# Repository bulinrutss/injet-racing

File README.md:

# INJET RACING

ECU de injeção para TBI (corpo de borboleta), Fase 1. Mede ar por velocidade e pressão (speed-density), calcula o tempo de injeção e aciona até quatro bicos em batch-fire. O cérebro é uma **Black Board STM32F407VET6** encaixada na placa; a fonte de 5 V fica na própria ECU.

A placa em curso é a **prodv6** (240 × 160 mm, duas camadas). O firmware em `firmware/` lê sensores, calcula o pulso e registra na serial. Ainda não dispara os bicos.

## Como funciona

A bateria entra por proteção (fusível, MOSFET contra inversão e TVS) e vira **+12V_PROT**. Esse 12 V alimenta bicos, bobinas de relé e o aquecedor da sonda pelo chicote. Um módulo **MP1584** gera **+5 V** para a Black Board, o MAP e os amplificadores da lambda. O 3,3 V sai do regulador interno da Black Board e é só distribuído na placa (sensores, pull-ups, opto de RPM). Não há um segundo LDO na ECU.

```
+12 V bateria
    │
    ├─ proteção ── +12V_PROT ── bicos (lado +), relés, aquecedor λ
    │
    └─ MP1584 ── +5 V ── Black Board ── +3V3 ── sensores e lógica
```

Cada volta do motor chega pelo **negativo da bobina**, isolado por um opto **PC817**. Com RPM, MAP, temperatura do ar e tensão da bateria, o firmware estima a massa de ar, aplica uma eficiência volumétrica (VE) e soma o tempo morto do bico. A sonda **LSU 4.2** (wideband, frente analógica com MCP6002 e OPA388IDR) devolve lambda; um PI corrige o pulso em até ±15 % com o motor quente e fora de plena carga. Os bicos são low-side: o chicote leva +12 V e a placa fecha o negativo com **IRLZ44N**. Três **2N7000** comandam relés externos (principal, bomba e IAC) pelo conector CN3. O relé em si não é soldado na placa.

Gravação e debug são pela USB da Black Board. Não há conector SWD na ECU.

| Ação | 12 V na ECU | Cabo USB |
|------|-------------|----------|
| Gravar firmware | desligado | normal |
| Monitor serial / tune | ligado | power blocker (só D+, D− e GND) |
| No carro | ligado | desconectado |

Serial de bancada: **115200 baud**.

## Estado agora

| Bloco | Situação |
|-------|----------|
| Proteção de 12 V e buck +5 V (MOD3–4) | roteado na prodv6 |
| Black Board, +3V3 e referência (MOD5) | roteado |
| Sensores IAT, CLT, MAP, TPS, tensão de bateria (MOD6) | roteado até os headers da Black Board |
| RPM pelo negativo da bobina (MOD7) | roteado, CN1-22 → PC817 → PE8 |
| Quatro injetores IRLZ44N (MOD8) | roteado, CN1-13…16 |
| Três drivers de relé + CN3 (MOD9) | roteado; SRD fica no chicote |
| Lambda e aquecedor (MOD11–12) | roteado |
| CAN (MOD10) | desativado nesta revisão |
| DRC, silk e Gerber | em aberto (clearance do OPA388, contorno da placa, unconnected cosmético) |
| Bancada sem motor | roteiro em `kicad/prodv6/BENCH-CHECKLIST.md`, ainda não é validação de rua |
| Firmware | referência de bancada: lê, calcula e loga; o pulso não sai nos MOSFETs |
| prodv7 | cópia da prodv6 com o OPA388 em DIP-8 no lado dos componentes |

O DRC da prodv6 ainda não está zerado. O checklist de layout e os scripts `_check_modN_now.py` estão em `kicad/prodv6/`.

## Placa

Abrir no KiCad 8:

`kicad/prodv6/injet-racing-prodv6.kicad_pro`

Salvar o PCB não mexe no esquemático. Atualizar o PCB a partir do esquemático é o F8. Não rodar o gerador Python por cima do `.kicad_pcb`: ele apaga trilhas e zonas já feitas.

A prodv7 (`kicad/prodv7/`) existe para trocar o OPA388 de SOIC na face de baixo por DIP-8 furado. O desenho de trabalho continua sendo a prodv6 até essa troca fechar.

### Conectores da prodv6

Pinagem que os scripts de checagem conferem na placa roteada. O restante do chicote está em `modulo/esquema-eletrico.md` §9.

**CN1** — header ATX 24 pinos (alimentação, sensores, RPM, bicos):

| Pinos | Função |
|-------|--------|
| 1–2 | +12V_BAT |
| 3 | +5 V (MAP) |
| 4 | +3V3 (TPS e pull-ups) |
| 6 | IAT |
| 7 | CLT |
| 8 | MAP |
| 10 | TPS |
| 11 | +12V_PROT (divisor de bateria) |
| 13–16 | INJ1…INJ4 (low-side) |
| 22 | RPM, negativo da bobina |

**CN2** — PCIe 6 pinos, sonda LSU:

| Pino | Função |
|------|--------|
| 1 | +12V_PROT, aquecedor H+ |
| 2 | H− (dreno do MOSFET) |
| 3 | sem ligação |
| 4 | IP |
| 5 | VM |
| 6 | UN |

**CN3** — PCIe 6 pinos, contato NA dos relés externos:

| Pino | Função |
|------|--------|
| 1 | IAC |
| 2 | bomba |
| 3 | relé principal |
| 4 | GND |

### GPIO da Black Board

Definidos em `firmware/include/pins.h` e no esquemático.

| Sinal | Pino |
|-------|------|
| IAT / CLT / MAP / TPS / VBat | PD0 / PA9 / PC9 / PC8 / PA8 |
| Lambda Vm, Ip, Un, Ri | PA4 / PA5 / PA6 / PE2 |
| Aquecedor | PB0 |
| RPM | PE8 |
| INJ1…4 | PE9, PE11, PE13, PE15 |
| Relé principal / bomba / IAC | PD10 / PD8 / PD9 |

## Firmware

Alvo: STM32F407VET6 pela core STM32duino (placa Generic F407VET6 ou equivalente da Black Board). Os fontes estão em `firmware/src/`; não há `platformio.ini` no repositório.

O `loop` faz isto a cada passagem:

1. Atualiza a wideband (aquecedor pela resistência da célula, corrente de bomba, lambda).
2. Lê MAP, TPS, CLT, IAT e bateria.
3. Atualiza o trim de lambda.
4. A cada 10 ms calcula o tempo de injeção em ms.
5. A cada 100 ms imprime `RPM MAP TPS CLT VBat L PW TRIM`.

O que esse código ainda não faz: agendar o pulso nos quatro MOSFETs (há um TODO no `main.cpp`), tabela VE de verdade (`fuelVeLookup` devolve 0,75 fixo) e protocolo de tune. A interrupção de RPM guarda o período; quem publica o valor filtrado é `rpmUpdate()`, e o `loop` ainda não chama essa função — por isso o campo RPM da serial fica em zero. A bomba é ligada no `setup` e permanece ligada.

Cilindrada, vazão dos bicos e número de cilindros em `fuel.cpp` / `pins.h` são constantes de bancada, não o acerto de um motor específico.

## Mapa do repositório

| Pasta | Conteúdo |
|-------|----------|
| `modulo/` | Esquema elétrico, listas de componentes, sensores, bicos, lambda, pinout e flanges |
| `kicad/prodv6/` | PCB atual, checklist, bancada e scripts de checagem |
| `kicad/prodv7/` | Variante com OPA388 em DIP-8 |
| `kicad/` | Esquemático hierárquico e PCBs anteriores (prod … prodv5) |
| `firmware/` | Firmware de referência da Fase 1 |
| `implementacoes-futuras/` | Ideias fora da Fase 1 (3-step, relé pesado, roda fônica, condicionador VR) |
| `projetos piloto/` | Produtos à parte, hoje o limitador 3-step |
| `assets/` | Renders e estudos de placa de uma camada |

Na raiz também estão o manual e a lista de TBI compatíveis (PDFs).

Itens de `implementacoes-futuras/` e de `projetos piloto/` ficam fora da prodv6 até serem puxados para o escopo.

## Licença

MIT. Copyright (c) 2026 Marcos Gasperin. Ver `LICENSE`.

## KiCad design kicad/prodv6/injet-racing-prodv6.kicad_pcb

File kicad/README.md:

# KiCad — INJET RACING ECU (Fase 1)

Projeto esquemático hierárquico gerado a partir de `modulo/esquema-eletrico.md`.

## Abrir

1. Instale [KiCad 8](https://www.kicad.org/download/) (ou 7 — formato compatível)
2. Abra **`injet-racing-ecu.kicad_pro`** no KiCad
3. No **Eeschema**, navegue pelas folhas na barra lateral ou duplo-clique nos blocos

## Folhas

| Página | Arquivo | Conteúdo |
|--------|---------|----------|
| 1 | `injet-racing-ecu.kicad_sch` | Índice hierárquico (blocos) |
| 2 | `sheets/power.kicad_sch` | 12V → fusível → IRF9540 → TVS → **MP1584** → +5V |
| 3 | `sheets/mcu.kicad_sch` | **Black Board** U1 + REF3033 + barra +3V3 |
| 4 | `sheets/sensors.kicad_sch` | IAT/CLT/MAP/TPS/VBat + CN1 ATX-24 |
| 5 | `sheets/rpm.kicad_sch` | PC817 opto (negativo bobina) |
| 6 | `sheets/injectors.kicad_sch` | 4× IRLZ44N low-side |
| 7 | `sheets/relays.kicad_sch` | 3× relé (principal/bomba/IAC) |
| 8 | `sheets/lambda.kicad_sch` | MCP6002 + OPA388IDR + heater + CN2 PCIe-6 |
| 9 | `sheets/can.kicad_sch` | SN65HVD230 transceiver |

## Regenerar

```powershell
cd kicad
pip install sexpdata
python _gen_kicad_ecu.py
```

## Notas

- **Símbolos embutidos** na biblioteca `Injet:*` — não precisa instalar libs externas para abrir
- **PCB vazio** — próximo passo: importar netlist e rotear (fenolite 1-layer ou PCB futuro)
- Após abrir, rode **Ferramentas → Associar footprints** e **Inspectar → Regras elétricas (ERC)**
- Se o KiCad pedir migrar formato, aceite — salve de volta na mesma pasta
- Pinagem GPIO = `firmware/include/pins.h` e `esquema-eletrico.md` §2.0

## Alimentação (resumo)

```
+12V_BAT → proteção → +12V_PROT
                    → MP1584 → +5V → Black Board pin 5V
                                      ↓ LDO interno
                                    +3V3 → barra ECU → sensores/CAN/opto
```

Não há AMS1117 extra na placa ECU — ver `esquema-eletrico.md` §1.4.

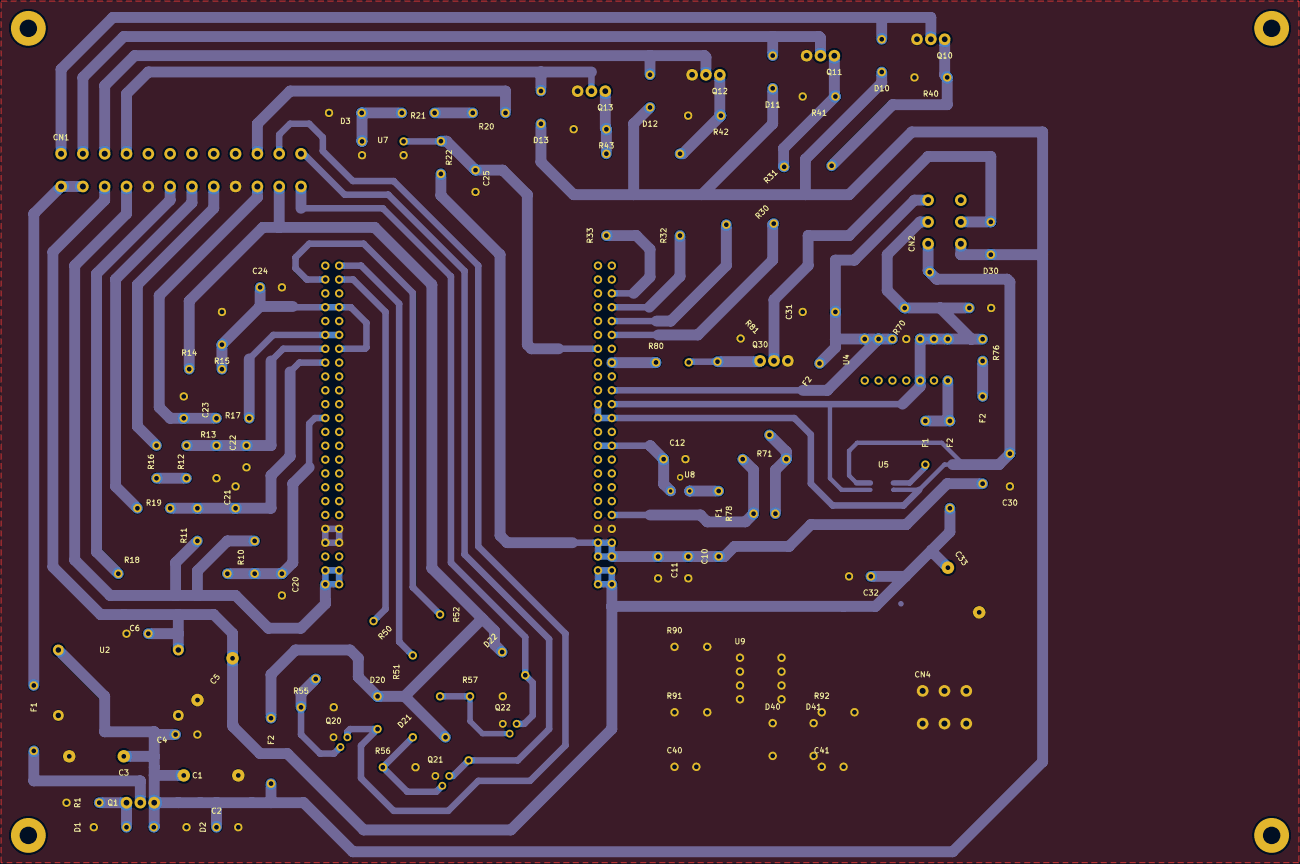
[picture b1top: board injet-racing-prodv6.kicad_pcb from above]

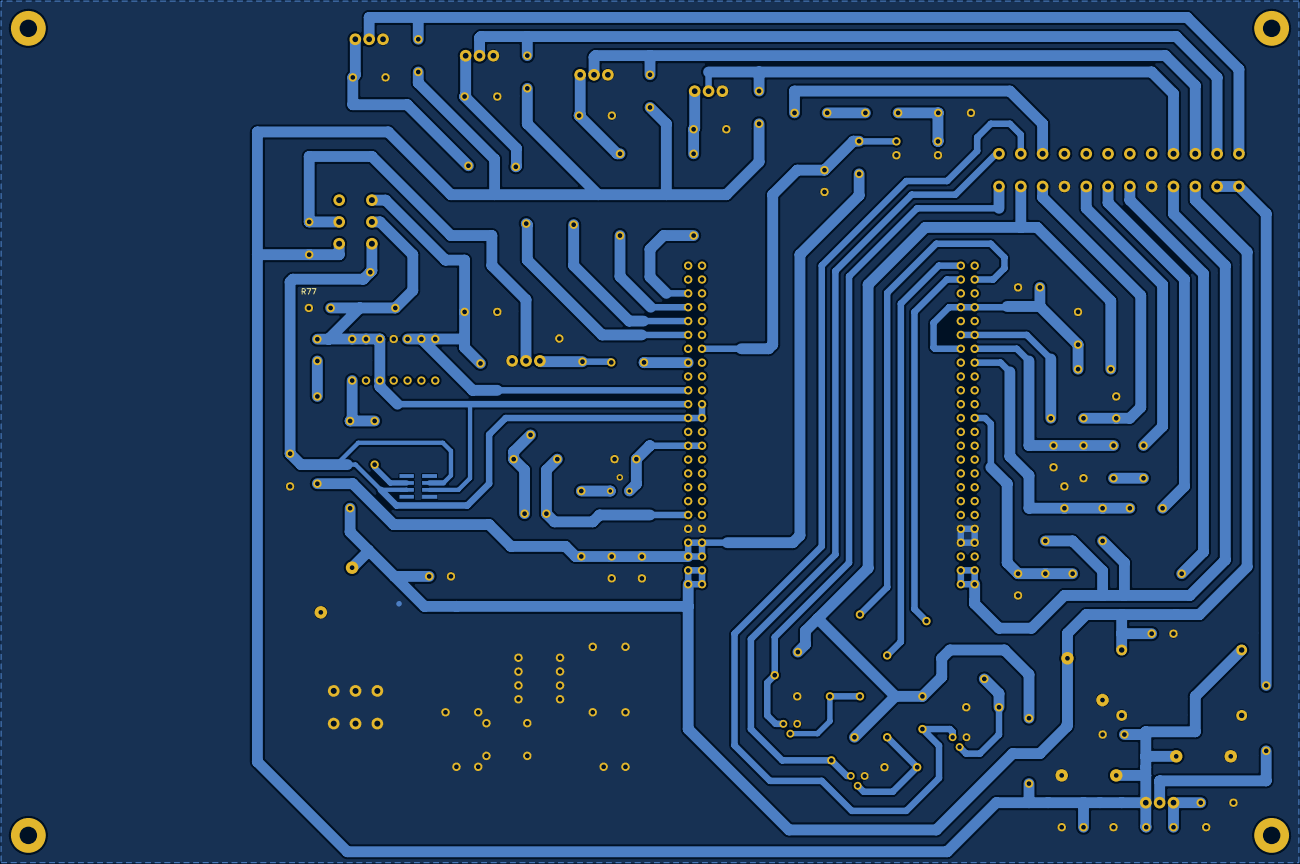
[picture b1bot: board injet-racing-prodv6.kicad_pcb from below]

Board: 2 copper layers, 102 parts (3 on the bottom side), 37 nets.

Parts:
C1: 220uF; C1
C2: 100nF; C2
C3: 100uF; C3
C4: 100nF; C4
C5: 220uF; C5
C6: 100nF; C6
C10: 100nF; C10
C11: 10uF; C11
C12: 10uF; C12
C20: 100nF; C20
C21: 100nF; C21
C22: 100nF; C22
C23: 100nF; C23
C24: 100nF; C24
C25: 1nF; C25
C30: 220nF; C30
C31: 220nF; C31
C32: 100nF; C32
C33: 10uF; C33
C40: 10nF; C40
C41: 1nF; C41
CN1: ATX-24; CN1
CN2: PCIe-6; CN2
CN4: PCIe-6 VR; CN2
D1: 15V Zener; D1
D2: TVS 33V; D2
D3: 1N4148; D3
D10: 1N4007; D10
D11: 1N4007; D11
D12: 1N4007; D12
D13: 1N4007; D13
D20: 1N4007; D20
D21: 1N4007; D21
D22: 1N4007; D22
D30: 1N4007; D30
D40: 1N4148; D40
D41: 1N4148; D41
F1, F1#2, F1#3, F2, F2#2, F2#3, F2#4: 5A; F1
H: MountingHole; MountingHole_3.2mm_M3
H#2, H#3, H#4: MountingHole; MountingHole_3.2mm_M3
Q1: IRF9540; QREV
Q10: IRLZ44N; Q10
Q11: IRLZ44N; Q11
Q12: IRLZ44N; Q12
Q13: IRLZ44N; Q13
Q20: 2N7000; Q20
Q21: 2N7000; Q21
Q22: 2N7000; Q22
Q30: IRLZ44N; Q30
R1: 100k; R1
R10, R11: 2.26k; R
R12, R40, R41, R42, R43, R55, R56, R57, R76, R77: 10k; R
R13: 18k; R13
R14, R91: 100k; R
R15: 10k; R15
R16, R17, R18, R19, R50, R51, R52: 1k; R
R20, R21: 10k 2W; R
R22, R92: 4k7; R
R30, R31, R32, R33, R80: 100R; R
R70: 61R9; R
R71: 6k8; R
R78: 1k; R78
R81: 10k; R81
R90: 47k; R
U1: STM32F4VE; BLACK_BOARD
U2: MP1584
U4: MCP6004; U6004
U5: OPA388IDR; U8628
U7: PC817
U8: REF3033; U8
U9: LM393

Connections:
+3V3: C10.A, C11.A, CN1.4, D40.K, F1#3.A, F1#3.B, F2#3.A, F2#3.B, R10.A, R11.A, R22.B, R76.A, R92.A, U1.L0I, U1.L0O, U1.L1I, U1.L1O, U1.R2I, U1.R2O, U1.R3I, U1.R3O, U8.1, U9.8
+5V: C5.A, C6.A, C32.A, C33.A, CN1.3, F1.A, F1.B, F2#4.A, F2#4.B, U1.R0I, U1.R0O, U1.R1I, U1.R1O, U2.3, U4.14, U5.7
+12V_BAT: CN1.1, CN1.2, F1#2.A
+12V_IN: F1#2.B, Q1.D
+12V_PROT: C1.A, C2.A, C3.A, C4.A, CN1.11, CN2.1, D2.A, D10.K, D11.K, D12.K, D13.K, D20.K, D21.K, D22.K, D30.K, F2.A, F2.B, Q1.S, R14.A, U2.1
CLT: C21.A, CN1.7, R11.B, R19.A, R19.B, U1.L16O
GHEAT: Q30.G, R80.A, R80.B, R81.A, U1.R16I
GINJ1: Q10.G, R30.A, R30.B, R40.A, U1.R18I
GINJ2: Q11.G, R31.A, R31.B, R41.A, U1.R19I
GINJ3: Q12.G, R32.A, R32.B, R42.A, U1.R20I
GINJ4: Q13.G, R33.A, R33.B, R43.A, U1.R21I
GND: C1.B, C2.B, C3.B, C4.B, C5.B, C6.B, C10.B, C11.B, C12.B, C20.B, C21.B, C22.B, C23.B, C24.B, C25.B, C30.B, C31.B, C32.B, C33.B, C40.B, C41.B, CN1.5, CN1.9, CN4.3, D1.K, D2.K, D3.A, D41.A, Q10.S, Q11.S, Q12.S, Q13.S, Q20.S, Q21.S, Q22.S, Q30.S, R1.B, R13.B, R15.B, R40.B, R41.B, R42.B, R43.B, R55.B, R56.B, R57.B, R77.B, R81.B, U1.L3I, U1.L3O, U1.L4I, U1.L4O, U1.R4I, U1.R4O, U2.2, U2.4, U4.4, U5.4, U7.2, U7.3, U8.2, U9.4
GRL1: Q20.G, R50.A, R50.B, R55.A, U1.L22I
GRL2: Q21.G, R51.A, R51.B, R56.A, U1.L23I
GRL3: Q22.G, R52.A, R52.B, R57.A, U1.L22O
H-: CN2.2, D30.A, Q30.D
IAT: C20.A, CN1.6, R10.B, R18.A, R18.B, U1.L12O
INJ1: CN1.13, D10.A, Q10.D
INJ2: CN1.14, D11.A, Q11.D
INJ3: CN1.15, D12.A, Q12.D
INJ4: CN1.16, D13.A, Q13.D
IP: C30.A, CN2.4, R70.A, U1.R12I, U1.R12O, U1.R13O, U5.2, U5.6
MAP: C22.A, CN1.8, R12.A, R12.B, R13.A, R16.A, R16.B, U1.L17O
QG: D1.A, Q1.G, R1.A
RI_PULSE: R71.B, R78.B, U1.R5I
RL1: CN1.23, D20.A, Q20.D
RL2: CN1.24, D21.A, Q21.D
RL3: CN1.12, D22.A, Q22.D
RPM_IN: C25.A, CN1.22, D3.K, R20.A, R20.B, R21.A, R21.B, R22.A, U1.R17O, U7.1, U7.4
RPM_VR: C41.A, R91.A, R92.B, U9.1
TPS: C23.A, CN1.10, R17.A, R17.B, U1.L18I, U1.L18O
UN: C31.A, CN2.6, F2#2.A, F2#2.B, R71.A, R78.A, U1.R14I, U4.5, U4.6, U4.7
VBAT: C24.A, R14.B, R15.A, U1.L17I, U1.L20I, U1.L20O
VM: CN2.5, R70.B, R76.B, R77.A, U1.R13I, U4.1, U4.2, U4.3, U4.12, U5.3
VR+: CN4.1, R90.A
VREF+: C12.A, U1.R10I, U1.R10O, U8.3
VR_LIM: C40.A, D40.A, D41.K, R90.B, R91.B, U9.2

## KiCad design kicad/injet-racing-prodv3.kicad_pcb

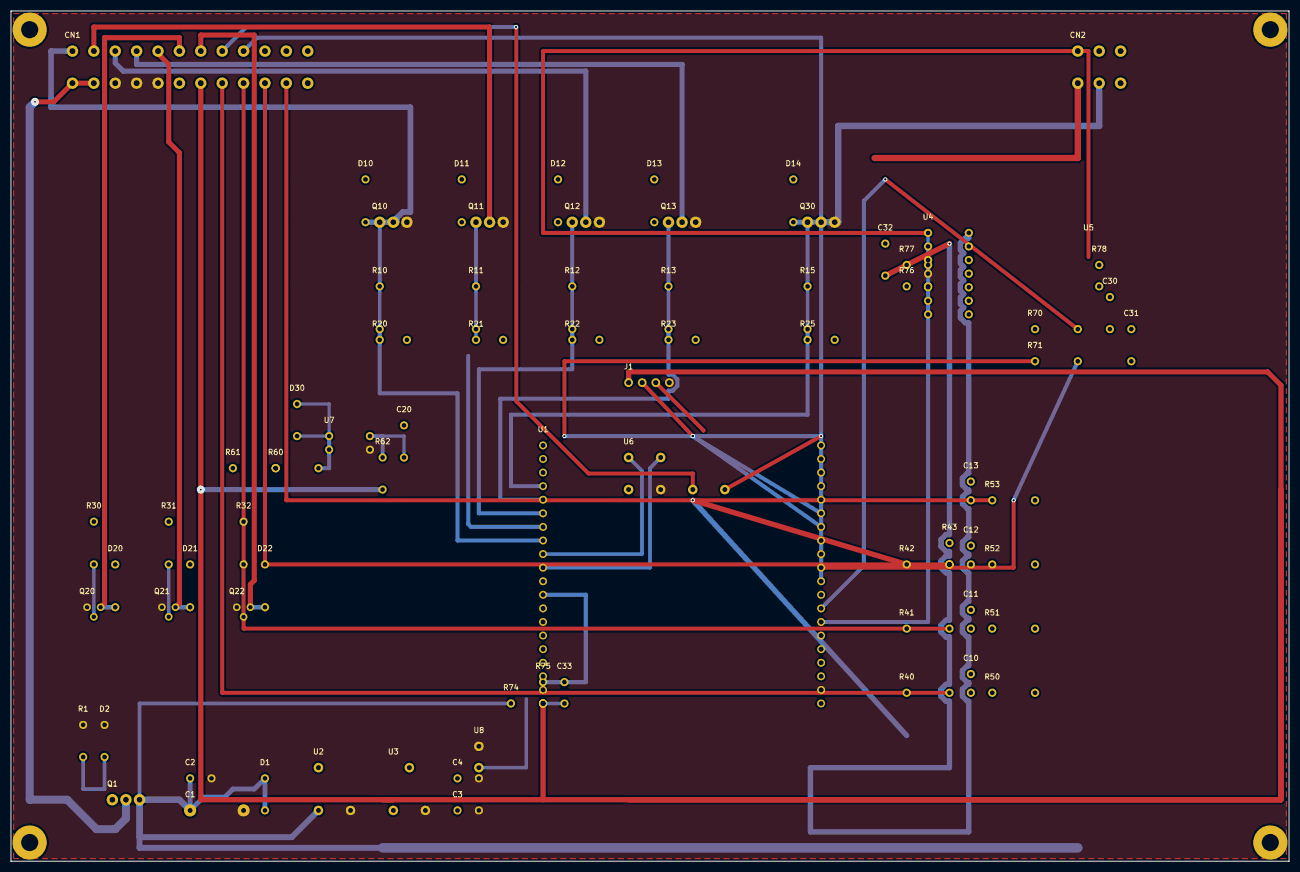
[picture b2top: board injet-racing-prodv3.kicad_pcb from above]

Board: 2 copper layers, 239.0 x 159.0 mm, 80 parts (0 on the bottom side), 40 nets.

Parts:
C1: C1
C2: C2
C3: C3
C4: C4
C10: C10
C11: C11
C12: C12
C13: C13
C20: C20
C30: C30
C31: C31
C32: C32
C33: C33
CN1: ATX-24; CN1
CN2: PCIe-6 λ; CN2
D1: D1
D2: D2
D10: D10
D11: D11
D12: D12
D13: D13
D14: D14
D20: D20
D21: D21
D22: D22
D30: D30
H: MountingHole_3.2mm_M3
H#2, H#3, H#4: MountingHole_3.2mm_M3
J1: SWD 4p; SWD
Q1: IRF9540; QREV
Q10: IRLZ44N; QINJ1
Q11: IRLZ44N; QINJ2
Q12: IRLZ44N; QINJ3
Q13: IRLZ44N; QINJ4
Q20: 2N7000; QRL1
Q21: 2N7000; QRL2
Q22: 2N7000; QRL3
Q30: IRLZ44N; QHEAT
R1: R1
R10: R10
R11: R11
R12: R12
R13: R13
R15: R15
R20: R20
R21: R21
R22: R22
R23: R23
R25: R25
R30: R30
R31: R31
R32: R32
R40: R40
R41: R41
R42: R42
R43: R43
R50: R50
R51: R51
R52: R52
R53: R53
R60: R60
R61: R61
R62: R62
R70: R70
R71: R71
R74: R74
R75: R75
R76: R76
R77: R77
R78: R78
U1: STM32F407 Black Board; MCU
U2: MP1584; BUCK
U3: LDO 3V3; LDO
U4: MCP6004; U6004
U5: AD8628; U8628
U6: SN65HVD230; CAN
U7: PC817; U817
U8: REF3033; U8

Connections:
+3V3: CN1.7, J1.1, R42.A, R62.A, R74.B, R75.A, U1.L1
+5V: C32.A, CN1.6, U4.14
+12V_IN: CN1.1, CN1.2, Q1.D
+12V_PROT: C1.A, C2.A, CN2.1, D1.A, D1.K, Q1.S, U2.VIN
CANH: CN1.20, U6.H
CANL: CN1.21, U6.L
CAN_RX: U1.L11, U6.RX
CAN_TX: U1.L12, U6.TX
CLT: CN1.9, R41.B
DAC_VM: R76.B, U1.R7, U4.1, U4.2, U4.5
GHEAT: Q30.G, R15.A, R15.B, R25.A, U1.L17
GINJ1: Q10.G, R10.A, R10.B, R20.A, U1.L13
GINJ2: Q11.G, R11.A, R21.A
GINJ3: Q12.G, R12.A, R12.B, R22.A, U1.L15
GINJ4: Q13.G, R13.A, R13.B, R23.A, U1.L16
GND: C1.B, C2.B, C3.B, C4.B, CN1.3, CN1.4, CN1.5, D2.K, J1.4, Q10.S, Q11.S, Q12.S, Q13.S, Q20.S, Q21.S, Q22.S, Q30.S, R1.B, U1.L2, U1.R2, U2.GND, U3.GND, U4.4, U5.4, U6.GND, U7.3, U8.GND
GRL1: Q20.G, R30.A
GRL2: Q21.G, R31.A
GRL3: Q22.G, R32.A
H-: CN2.2, D14.A, Q30.D
IAT: CN1.8, R40.B
INJ1: CN1.13, D10.A, Q10.D
INJ2: CN1.14, Q11.D
INJ3: CN1.15, Q12.D
INJ4: CN1.16, Q13.D
IP: CN2.3, R70.B, U1.R8
MAP: CN1.10, D22.K, R42.B, R43.A
QG: D2.A, R1.A
RI_PULSE: R71.B, U1.R11
RL1: CN1.18, D20.A, Q20.D
RL2: CN1.17, D21.A, Q21.D
RL3: CN1.19, D22.A, Q22.D
RPM_IN: CN1.12, D30.A, D30.K, R60.B, U7.1, U7.2
RPM_OUT: C20.A, R62.B, U7.4
SWCLK: J1.3, U1.R15
SWDIO: J1.2, U1.R14
TPS: CN1.11, R53.A
UN: CN2.5, R71.A, U1.R10
VBAT: C33.A, R74.A, R75.B, U1.L9
VM: CN2.4, U5.3

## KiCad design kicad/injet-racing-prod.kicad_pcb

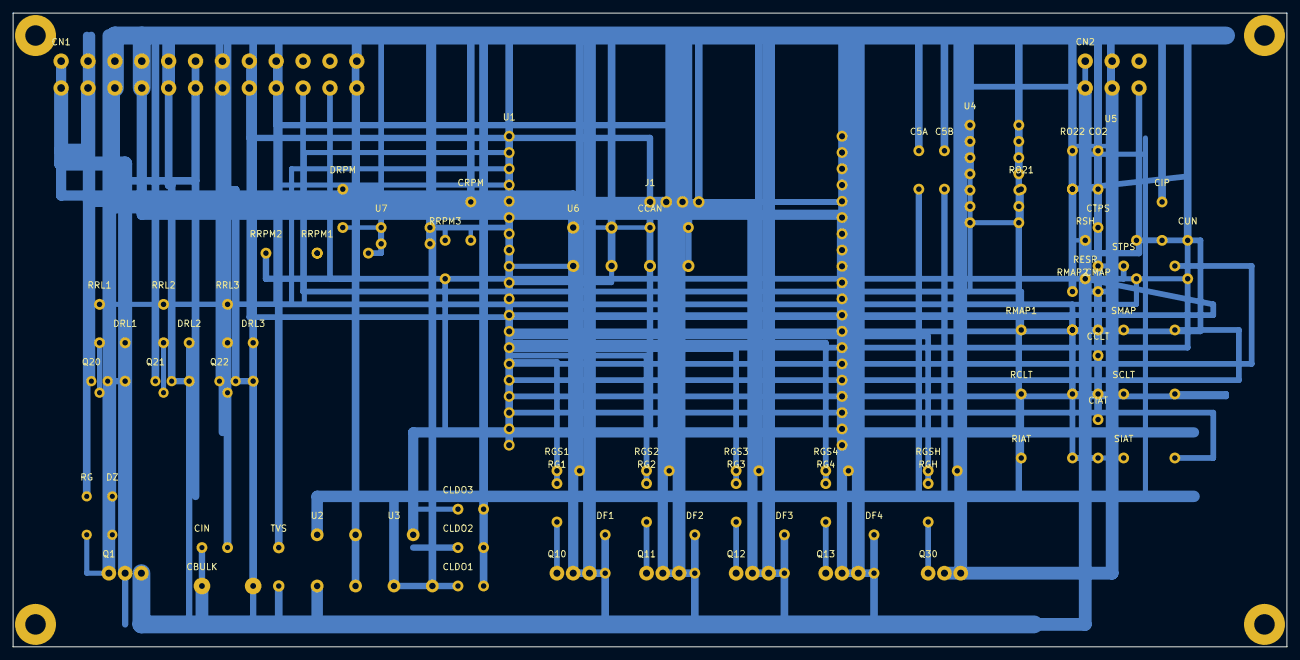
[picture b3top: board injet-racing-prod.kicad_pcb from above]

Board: 2 copper layers, 199.0 x 99.0 mm, 78 parts (0 on the bottom side), 37 nets.

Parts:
C5A: C5A
C5B: C5B
CBULK: CBULK
CCAN: CCAN
CCLT: CCLT
CIAT: CIAT
CIN: CIN
CIP: CIP
CLDO1: CLDO1
CLDO2: CLDO2
CLDO3: CLDO3
CMAP: CMAP
CN1: ATX-24; CN1
CN2: PCIe-6 λ; CN2
CO2: CO2
CRPM: CRPM
CTPS: CTPS
CUN: CUN
DF1: DF1
DF2: DF2
DF3: DF3
DF4: DF4
DRL1: DRL1
DRL2: DRL2
DRL3: DRL3
DRPM: DRPM
DZ: DZ
H: MountingHole_3.2mm_M3
H#2, H#3, H#4: MountingHole_3.2mm_M3
J1: SWD 4p; SWD
Q1: IRF9540; QREV
Q10: IRLZ44N; QINJ1
Q11: IRLZ44N; QINJ2
Q12: IRLZ44N; QINJ3
Q13: IRLZ44N; QINJ4
Q20: 2N7000; QRL1
Q21: 2N7000; QRL2
Q22: 2N7000; QRL3
Q30: IRLZ44N; QHEAT
RCLT: RCLT
RESR: RESR
RG: RG
RG1: RG1
RG2: RG2
RG3: RG3
RG4: RG4
RGH: RGH
RGS1: RGS1
RGS2: RGS2
RGS3: RGS3
RGS4: RGS4
RGSH: RGSH
RIAT: RIAT
RMAP1: RMAP1
RMAP2: RMAP2
RO21: RO21
RO22: RO22
RRL1: RRL1
RRL2: RRL2
RRL3: RRL3
RRPM1: RRPM1
RRPM2: RRPM2
RRPM3: RRPM3
RSH: RSH
SCLT: SCLT
SIAT: SIAT
SMAP: SMAP
STPS: STPS
TVS: TVS
U1: STM32F407 Black Board; MCU
U2: MP1584; BUCK
U3: LDO 3V3; LDO
U4: MCP6004; U6004
U5: AD8628; U8628
U6: SN65HVD230; CAN
U7: PC817; U817

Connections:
+3V3: CCAN.A, CLDO2.A, CLDO3.A, CN1.7, J1.1, RCLT.A, RIAT.A, RRPM3.A, U1.L1, U1.L16, U3.OUT, U6.TX, U6.VCC
+5V: C5A.A, C5B.A, CLDO1.A, CN1.6, U1.R1, U2.VOUT, U3.IN, U4.14, U5.8
+12V_IN: CN1.1, CN1.2, Q1.D
+12V_PROT: CBULK.A, CIN.A, CN2.1, DF1.K, DF2.K, DF3.K, DF4.K, DRL1.K, DRL2.K, DRL3.K, Q1.S, TVS.A, U2.VIN
CANH: CN1.20, U6.H
CANL: CN1.21, U6.L
CAN_RX: U1.L11, U6.RX
CLT: CCLT.A, CN1.9, RCLT.B, SCLT.A, SCLT.B, U1.L4
GHEAT: Q30.G, RGH.A, RGH.B, RGSH.A, U1.L20
GINJ1: Q10.G, RG1.A, RG1.B, RGS1.A, U1.L6, U1.L13
GINJ2: Q11.G, RG2.A, RG2.B, RGS2.A, U1.L14
GINJ3: Q12.G, RG3.A, RG3.B, RGS3.A, U1.L7, U1.L15
GINJ4: Q13.G, RG4.A, RG4.B, RGS4.A
GND: C5A.B, C5B.B, CBULK.K, CCAN.B, CCLT.B, CIAT.B, CIN.K, CIP.B, CLDO1.B, CLDO2.B, CLDO3.B, CMAP.B, CN1.3, CN1.4, CN1.5, CN1.24, CO2.B, CRPM.B, CTPS.B, CUN.B, DZ.K, J1.4, Q1.G, Q10.S, Q11.S, Q12.S, Q13.S, Q20.S, Q21.S, Q22.S, Q30.S, RG.B, RGS1.B, RGS2.B, RGS3.B, RGS4.B, RGSH.B, RMAP2.B, RO22.B, TVS.K, U1.L2, U1.R2, U2.GND, U3.GND, U4.4, U4.11, U5.4, U6.GND, U7.3
GRL1: Q20.G, RRL1.A, RRL1.B, U1.L17
GRL2: Q21.G, RRL2.A, RRL2.B, U1.L18
GRL3: Q22.G, RRL3.A, RRL3.B, U1.L19
H-: CN2.2, Q30.D
IAT: CIAT.A, CN1.8, RIAT.B, SIAT.A, SIAT.B, U1.L3
INJ_FLY: DF1.A, DF2.A, DF3.A, DF4.A, Q10.D, Q11.D, Q12.D, Q13.D
IP: CIP.A, CN2.3, RSH.A, RSH.B, U1.L8
IP_DRV: U5.2, U5.6
MAP: CN1.10, RMAP1.A, RMAP1.B, RMAP2.A
MAP_ADC: SMAP.B, U1.L5
MAP_MID: CMAP.A, SMAP.A
O2: CO2.A, RO21.A, RO21.B, RO22.A, U4.7
QG: DZ.A, RG.A
RI_PULSE: RESR.B, U1.R8
RL_FLY: DRL1.A, DRL2.A, DRL3.A, Q20.D, Q21.D, Q22.D
RPM_IN: CN1.12, RRPM1.A, RRPM1.B, RRPM2.A, RRPM2.B, U7.1
RPM_LED: DRPM.A, DRPM.K, U7.2
RPM_OUT: CRPM.A, RRPM3.B, U1.L10, U7.4
SWCLK: J1.3, U1.R5
SWDIO: J1.2, U1.R4, U1.R16
TPS: CN1.11, CTPS.A, STPS.A, STPS.B
UN: CN2.5, CUN.A, RESR.A, U1.L9
VM: CN2.4, U1.R3, U4.1, U4.2, U4.3, U5.3

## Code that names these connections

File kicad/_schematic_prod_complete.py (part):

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    d.add(gen.label_global("+3V3", mx + 58, my + 5, "output"), gen.wire_h(mx + 55, mx + 65, my + 5))

    # GPIO → nets (fio + label para drivers/sensores)
    gpio_map = [
        ("PA0", "IAT"), ("PA1", "CLT"), ("PA2", "MAP"), ("PA3", "TPS"),
        ("PA4", "VM"), ("PA5", "IP"), ("PA6", "UN"), ("PC0", "RI_PULSE"), ("PC1", "VBAT"),
        ("PB0", "RPM_OUT"), ("PB8", "CAN_RX"), ("PB9", "CAN_TX"),
        ("PE9", "GINJ1"), ("PE11", "GINJ2"), ("PE13", "GINJ3"), ("PE14", "GINJ4"),
        ("PD8", "GRL1"), ("PD9", "GRL2"), ("PD10", "GRL3"), ("PD12", "GHEAT"),
    ]
    gx = mx + 45
    for i, (mcu, net) in enumerate(gpio_map):
        gy = my + 25 - i * 4.5
        d.add(gen.wire_h(mx + 20, gx, my + 15.24 - i * 2.54 if i < 20 else gy),
              gen.label_local(net, gx + 2, gy))
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    d.add(gen.wire_h(sx - 3.5, sx + 2.5, y), gen.wire_v(sx + 15, y, y + 5.5),
          gen.wire_h(sx + 15, sx + 15, y + 8), gen.wire_h(sx + 2.5, sx + 47.5, y))
    gen.place_gnd(d, sx + 15, y + 8)
    d.add(gen.label_local("MAP", sx + 62, y))

    # TPS
    y = sy + 54
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    gen.place_r(d, "R17", "1k", sx + 45, y)
    d.add(gen.label_global("+3V3", sx - 8, y, "passive"), gen.wire_h(sx - 8, sx + 42.5, y))
    gen.place_gnd(d, sx + 10, y + 8)
    d.add(gen.label_local("TPS", sx + 62, y))

    # VBat
    y = sy + 72
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    gen.place_gnd(d, sx + 15, y + 8)
    d.add(gen.label_local("VBAT", sx + 62, y))

    # MAP +5V → CN1-6, +3V3 → CN1-7 (labels globais já ligam)

    # =========================================================================
    # RPM — PC817 → CN1-12
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    gen.place_r(d, "R22", "4k7", rx + 25, ry + 5)
    gen.place_d(d, "D3", "1N4148", rx - 5, ry - 5)
    gen.place_c(d, "C25", "1nF", rx + 35, ry)
    d.add(gen.label_global("RPM_IN", rx - 35, ry + 10, "input"),
          gen.wire_h(rx - 35, rx - 27.5, ry + 10), gen.wire_h(rx - 12.5, rx - 7.5, ry + 10))
    d.add(gen.wire_h(rx - 7.5, rx - 5, ry - 5), gen.wire_h(rx + 7.5, rx + 30, ry + 5))
    d.add(gen.label_global("RPM_OUT", rx + 42, ry, "output"), gen.wire_h(rx + 37.5, rx + 42, ry))
    gen.place_gnd(d, rx - 5, ry - 5)
    gen.place_v33(d, rx - 35, ry + 20)
    gen.place_gnd(d, rx - 35, ry - 5)
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    d.sym("Injet:SN65HVD230", "U6", "SN65HVD230", cx, cy)
    gen.place_c(d, "C40", "100nF", cx - 20, cy + 8)
    gen.place_c(d, "C41", "10uF", cx - 20, cy + 3)
    d.add(gen.label_global("CAN_TX", cx - 28, cy + 5, "input"),
          gen.wire_h(cx - 28, cx - 12.5, cy + 5))
    d.add(gen.label_global("CAN_RX", cx - 28, cy - 2, "output"),
          gen.wire_h(cx - 28, cx - 12.5, cy - 2))
    gen.place_v33(d, cx - 28, cy + 15)
    gen.place_gnd(d, cx - 28, cy - 10)
    d.add(gen.label_global("CANH", cx + 25, cy + 5, "bidirectional"),
          gen.wire_h(cx + 12.5, cx + 35, cy + 5))
    d.add(gen.label_global("CANL", cx + 25, cy - 2, "bidirectional"),
          gen.wire_h(cx + 12.5, cx + 35, cy - 2))

    # =========================================================================
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    gen.place_r(d, "R80", "100R", lx + 95, ly)
    gen.place_r(d, "R81", "10k", lx + 110, ly + 12)
    gen.place_d(d, "D30", "1N4007", lx + 125, ly - 8)
    d.add(gen.label_global("GHEAT", lx + 88, ly, "input"), gen.wire_h(lx + 88, lx + 92.5, ly))
    d.add(gen.label_global("H_MINUS", lx + 135, ly, "output"), gen.wire_h(lx + 112.5, lx + 145, ly))
    d.add(gen.label_global("+12V_PROT", lx + 135, ly + 8, "passive"),
          gen.wire_h(lx + 130, lx + 145, ly + 8), gen.wire_v(lx + 130, ly - 8, ly + 8))
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
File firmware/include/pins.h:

#pragma once

// INJET RACING — pinagem fixada STM32F407 Fase 1
// Ver esquema-eletrico.md §3.5 e ecu-pcb-1layer-netlist.md

// --- Sensores ADC (J2 esquerda — L12O/L16O/L17O/L17I/L18I) ---
#define PIN_IAT   PD0   // L12O ADC123_IN0
#define PIN_CLT   PA9   // L16O ADC123_IN1
#define PIN_MAP   PC9   // L17O ADC123_IN9
#define PIN_TPS   PC8   // L18I ADC123_IN8  (L18O=PC7 trilha bypass)
#define PIN_VBAT  PA8   // L17I ADC123_IN8  (L20I/O trilha bypass)

// --- Lambda wideband DIY ---
#define PIN_DAC_VM    PA4   // DAC1 — terra virtual Vm (~2,5 V)
#define PIN_ADC_IP    PA5   // corrente bomba (shunt 61,9 Ω)
#define PIN_ADC_UN    PA6   // célula Nernst
#define PIN_HEATER    PB0   // R16I PWM aquecedor MOSFET
#define PIN_RI_PULSE  PE2   // R5I pulso Ri (mede resistência Nernst)

// --- RPM ---
#define PIN_RPM   PE8       // R17O — EXTI falling edge (opto PC817)

// --- CAN ---
#define PIN_CAN_RX  PB8
#define PIN_CAN_TX  PB9

// --- Injetores (batch-fire) ---
#define PIN_INJ1  PE9
#define PIN_INJ2  PE11
#define PIN_INJ3  PE13
#define PIN_INJ4  PE15

// --- Relés ---
#define PIN_RL_MAIN  PD10  // L22I GRL1
#define PIN_RL_PUMP  PD8   // L23I GRL2
#define PIN_RL_IAC   PD9   // L22O GRL3

// --- ADC ---
#define ADC_VREF_V       3.3f
#define ADC_MAX_COUNTS   4095.0f

// Divisor VBat 100k / 10k
#define VBAT_R_HI_OHMS   100000.0f
#define VBAT_R_LO_OHMS   10000.0f
#define VBAT_DIV_RATIO   ((VBAT_R_HI_OHMS + VBAT_R_LO_OHMS) / VBAT_R_LO_OHMS)

// Lambda LSU 4.2 (padrão)
#define WB_SHUNT_OHMS    61.9f
#define WB_RI_TARGET_OH  80.0f      // Ω @ ~780 °C
#define WB_UN_TARGET_V   0.450f
#define WB_R_ESR_OHMS    6800.0f   // 6k8 para LSU 4.2

// Motor
#define ENGINE_CYLINDERS 6          // 4 ou 6 — configurável
#define RPM_MIN_VALID    200.0f     // abaixo = falha/parado — não atualiza filtro
#define RPM_MAX_VALID    7000.0f    // acima = ringing/lixo — não atualiza filtro
// Debounce ISR (µs): deve ser < período em RPM_MAX_VALID.
// 6 cil @ 7000 → período ≈ 2857 µs; 2500 deixa margem e ainda corta ringing.
// No carro: ↑ se contar pulso duplo; ↓ se RPM alto “travar” cedo.
#define RPM_DEBOUNCE_US  2500u
#define STOICH_AFR       14.7f
